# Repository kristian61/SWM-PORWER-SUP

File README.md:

# SWM-PORWER-SUP – laboratorieforsyning 100 V / 40 A

**Status: uafsluttet konstruktionsudkast. Den komplette 4 kW strømforsyning er ikke leveret eller frigivet til fremstilling.**

## Download

Afleveringsfilerne ligger direkte i dette repository:

- [Dansk PDF-manual, 134 sider](https://github.com/kristian61/SWM-PORWER-SUP/raw/refs/heads/main/exports/manual_da.pdf)
- [Komplet projekt-ZIP med fabrikantdatablade, cirka 61 MB](https://github.com/kristian61/SWM-PORWER-SUP/raw/refs/heads/main/exports/psu_design_draft.zip)
- [Mindre projekt-ZIP uden fabrikantdatablade, cirka 15 MB](https://github.com/kristian61/SWM-PORWER-SUP/raw/refs/heads/main/exports/psu_design_compact.zip)
- [SHA-256-kontrolsummer](exports/download_SHA256SUMS.txt)

PDF, ZIP og kontrolrapporter er den kontrollerede CAD-aflevering fra 10. oktober 2026, før GitHub-upload. Deres bemærkninger om endnu ikke udført GitHub-publicering beskriver dette tidligere tidspunkt. Kildefilerne på main indeholder samme CAD og beregningsarbejde samt disse downloadhenvisninger. Upload betyder ingen frigivelse til fremstilling eller net-/effekttest. Nogle scripts i den mindre ZIP kræver originalerne fra den komplette pakke.

Krav: 230 V AC på en dedikeret 32 A kreds, isoleret og flydende 0–100 V udgang, op til 40 A og justerbar strømbegrænsning til små prøveprint.

## Konkrete delprojekter

| Delprojekt | Leveret | Kontrolstatus |
|---|---|---|
| Passivt måle-/testkort | Native KiCad-diagram og fuldt routet 110 × 90 mm, 2-lags PCB, 11 testpunkter | ERC/DRC uden fejl, ingen åbne forbindelser, alle 52 pin/pad-forbindelser sammenholdt; HV-reglernes aktivering afprøvet |
| LTC3779-effektfase | To-siders diagram, lokal controller-symbol/footprint, BOM, 19 testpunkter og fuldt routet 135 × 90 mm PCB i fire lag | ERC/DRC/paritet uden fejl, ingen åbne forbindelser; 175 logiske pins og alle 191 fysiske pads kontrolleret |
| Isoleret netdel | Native chassisdiagram for 2 × RSP-3000-48 ved 55 V hver, separate enable-kredse, lokale senseledninger og diodekrav | Officielle producentdata og terminalforbindelser kontrolleret, ERC bestået; ingen net-PCB eller kvalificeret systemintegration |
| Analogt CV/CC-styrekort | Separat forsøgsdiagram, fuldt routet 180 × 150 mm PCB, komponentliste og 16 testpunkter til én effektfase | ERC/DRC/paritet bestået, alle 211 forbindelser stemmer; regulering og fejlrespons utestet, omfatter ikke 0 V, milliamperebeskyttelse eller 40 A |

Effektfaseudkastet har fast 99,6 V, 10 A som uverificeret udviklingsmål og en intern fast strømgrænse omkring 12,5 A. Det er ikke en 0–100 V / 40 A laboratorieforsyning og har ingen justerbar laboratorie-CC. Der er endnu ingen hardwaretest af nogen af kortene.

Det separate styrekort undersøger en positiv VFB-injektion til CV og en ITH-clamp til CC. Det er ikke integreret i den oprindelige faste effektfase. Nominelle kommandoer dækker cirka 1,2–100 V og 0–10 A, men de aktuelle hardwarevinduer slukker ved strømkommandoer under cirka 0,21 A. Det kan derfor ikke bruges som dokumenteret beskyttelse af et lille opamp-print.

## Filer

- `design/measurement/measurement.kicad_pro`: målekortets native KiCad-projekt.
- `design/power/power_phase.kicad_pro`: det uafsluttede enkeltfase-projekt.
- `design/frontend/frontend.kicad_pro`: netmodulernes chassisforbindelser; `exports/frontend/frontend.pdf` er det to-siders PDF-diagram.
- `design/control/control.kicad_pro`: separat eksperimentelt analogt styrekort med routet PCB.
- `bom/measurement.csv` og `bom/power-phase.csv`: alle komponentreferencer, værdier, mængder, footprints, funktioner og indkøbs-/reviewstatus for hvert kort. Referencer som R1 og J1 starter forfra på hvert delprojekt.
- `bom/current-draft.csv`: samlet komponentoversigt med eksplicit kortnavn; den er ikke en komplet 4 kW-stykliste.
- `bom/critical-components.csv` og `docs/component-qualification.md`: 85 kritiske komponentposter med fabrikantdata, pinout, betingelser og åbne valg.
- `design/control/studies/`, `bom/phase-balancing-study.csv` og `docs/phase-balancing.md`: nyt énkanals fasestrømstudie og model af fire uafhængige strømservoer; ikke integreret i de routede kort.
- `docs/bus-disconnect-design.md`: betinget dimensionering af fysisk busafbrydelse; komponent- og transientkvalifikation mangler.
- `docs/final-status.md`: afsluttende status opdelt i CAD, kontroller, beregninger, simulering og fysisk validering.
- `bom/frontend.csv`: netmoduler og alle viste chassisdele; manglende varenumre/rating står som krav, ikke indkøbsfrigivne komponenter.
- `bom/control.csv` og `docs/control.md`: styrekortets komponenter, funktion, stik, testpunkter og aktuelle begrænsninger.
- `docs/control-layout.md`, `docs/power-analysis.md`, `docs/bus-protection.md` og `docs/low-current-output.md`: layout, tab/ripple/loop-modeller, busfejl og mA-/0 V-undersøgelse.
- `docs/low-current-loop.md`: separat antaget post-bulk-strømservo og varm-SOA-begrænsning; ingen frigivet lavstrøms-PCB.
- `docs/power-layout.md` og `exports/power/remaining_connections.json`: effektkortets strømbaner, kobberbudget, regler og konkrete routingrester.
- `docs/manual.md` og `docs/power-phase.md`: funktion, stik, testpunkter og fejlfinding.
- `docs/krav.md`, `docs/architecture-research.md`, `docs/frontend-selection.md` og `docs/protection-and-test-plan.md`: krav, effektbudget, isolation/netdel og fysisk valideringsplan.
- `exports/manual_da.pdf`: samlet dansk projektmanual.
- `exports/measurement/` og `exports/power/`: PDF-diagrammer og PCB-visninger.
- `exports/verification/`: kontroller og samlet status. Ingen Gerber-frigivelse.
- `exports/verification/project_status.json`: samlet CAD-status, beregningsrapporter, kildehashes og manglende hardwarevalidering.
- `references/`: hentede officielle producentdatablade og referencekredsløb.

## KiCad i cloudmiljøet

KiCad 9.0.2 er allerede installeret. Brug wrapperen, fordi hjemmemappen er skrivebeskyttet:

```sh
cd /workspace/SWM-PORWER-SUP
bin/kicad-env kicad-cli version
bin/kicad-env /usr/bin/python3 scripts/validate_kicad.py
bin/kicad-env /usr/bin/python3 scripts/check_inventory.py
bin/kicad-env /usr/bin/python3 scripts/validate_control_layout.py
```

Python PCB-API'en findes i `/usr/bin/python3`, ikke standard-Python. Brug den eksisterende checkout; cloudopgaven er allerede isoleret, så opret ikke en Git worktree som opstartstrin.

Kun ved bevidst regeneration af genererede filer:

```sh
bin/kicad-env /usr/bin/python3 scripts/measurement_gen.py
bin/kicad-env /usr/bin/python3 scripts/power_phase_gen.py
bin/kicad-env /usr/bin/python3 scripts/frontend_gen.py
bin/kicad-env /usr/bin/python3 scripts/control_gen.py
bin/kicad-env /usr/bin/python3 scripts/control_route.py
/usr/bin/python3 scripts/package_draft.py --metadata-only
/usr/bin/python3 scripts/project_status.py
/usr/bin/python3 scripts/render_manual.py
/usr/bin/python3 scripts/package_draft.py
```

Beregningsmodeller kan køres særskilt med `/usr/bin/python3`: design_calcs.py, power_analysis.py, control_limits.py, low_current_calcs.py, low_current_loop.py, phase_balance_analysis.py, bus_protection_calcs.py og bus_disconnect_envelope.py. Kør design_calcs.py efter bus_disconnect_envelope.py for det konsistente tillægsbudget. De aktuelle resultater og modelantagelser ligger i exports/analysis/.

Generatorerne overskriver deres genererede KiCad-filer. Bevar brugerændringer først. Efter control_gen.py skal control_route.py genoprette routingen. Den afsluttende validate_control_layout.py opdaterer aktuel status; summary_pre_route.json viser generatorstadiet. power_phase_gen.py genafspiller den gemte slutrouting fra power_routing_plan.json; en isoleret regeneration er kontrolleret.

## Hvad der blokerer den komplette konstruktion

Front-endens arbejdsvalg er nu dokumenteret: 2 × RSP-3000-48 ved 55 V giver nominelt 110 V. Der mangler modelkvalifikation af seriedrift/flydende offset, endelige chassis-/effektkomponenter, busbeskyttelse, færdig og integreret CV/CC samt 0 V-regulering, lavstrømsbeskyttelse, firefaset systemintegration og fysisk validering. Modulernes OVP kan tillade samlet 134,4 V threshold og ukendt oversving; det overholder ikke automatisk effektfasens 120 V-proceduregrænse. Færdig CAD-routing ændrer ikke disse funktionelle og sikkerhedsmæssige blokeringer.

Analog Devices, TI, `meanwell.com` og aktuelle Infineon-produkt-/assetadresser kan nås, og de læste originaler er gemt i `references/`. `www.diodes.com` gav fortsat HTTP 403 ved de seneste normale forsøg. Netværksdomæner og genbrugelige KiCad-opstartsinstruktioner er gemt i miljøkladden. Gennemgå og gem ændringerne i miljøindstillingerne for genbrug; en kladdesave publicerer ikke miljøet. Publicering og afprøvning i en ny task er ikke udført.

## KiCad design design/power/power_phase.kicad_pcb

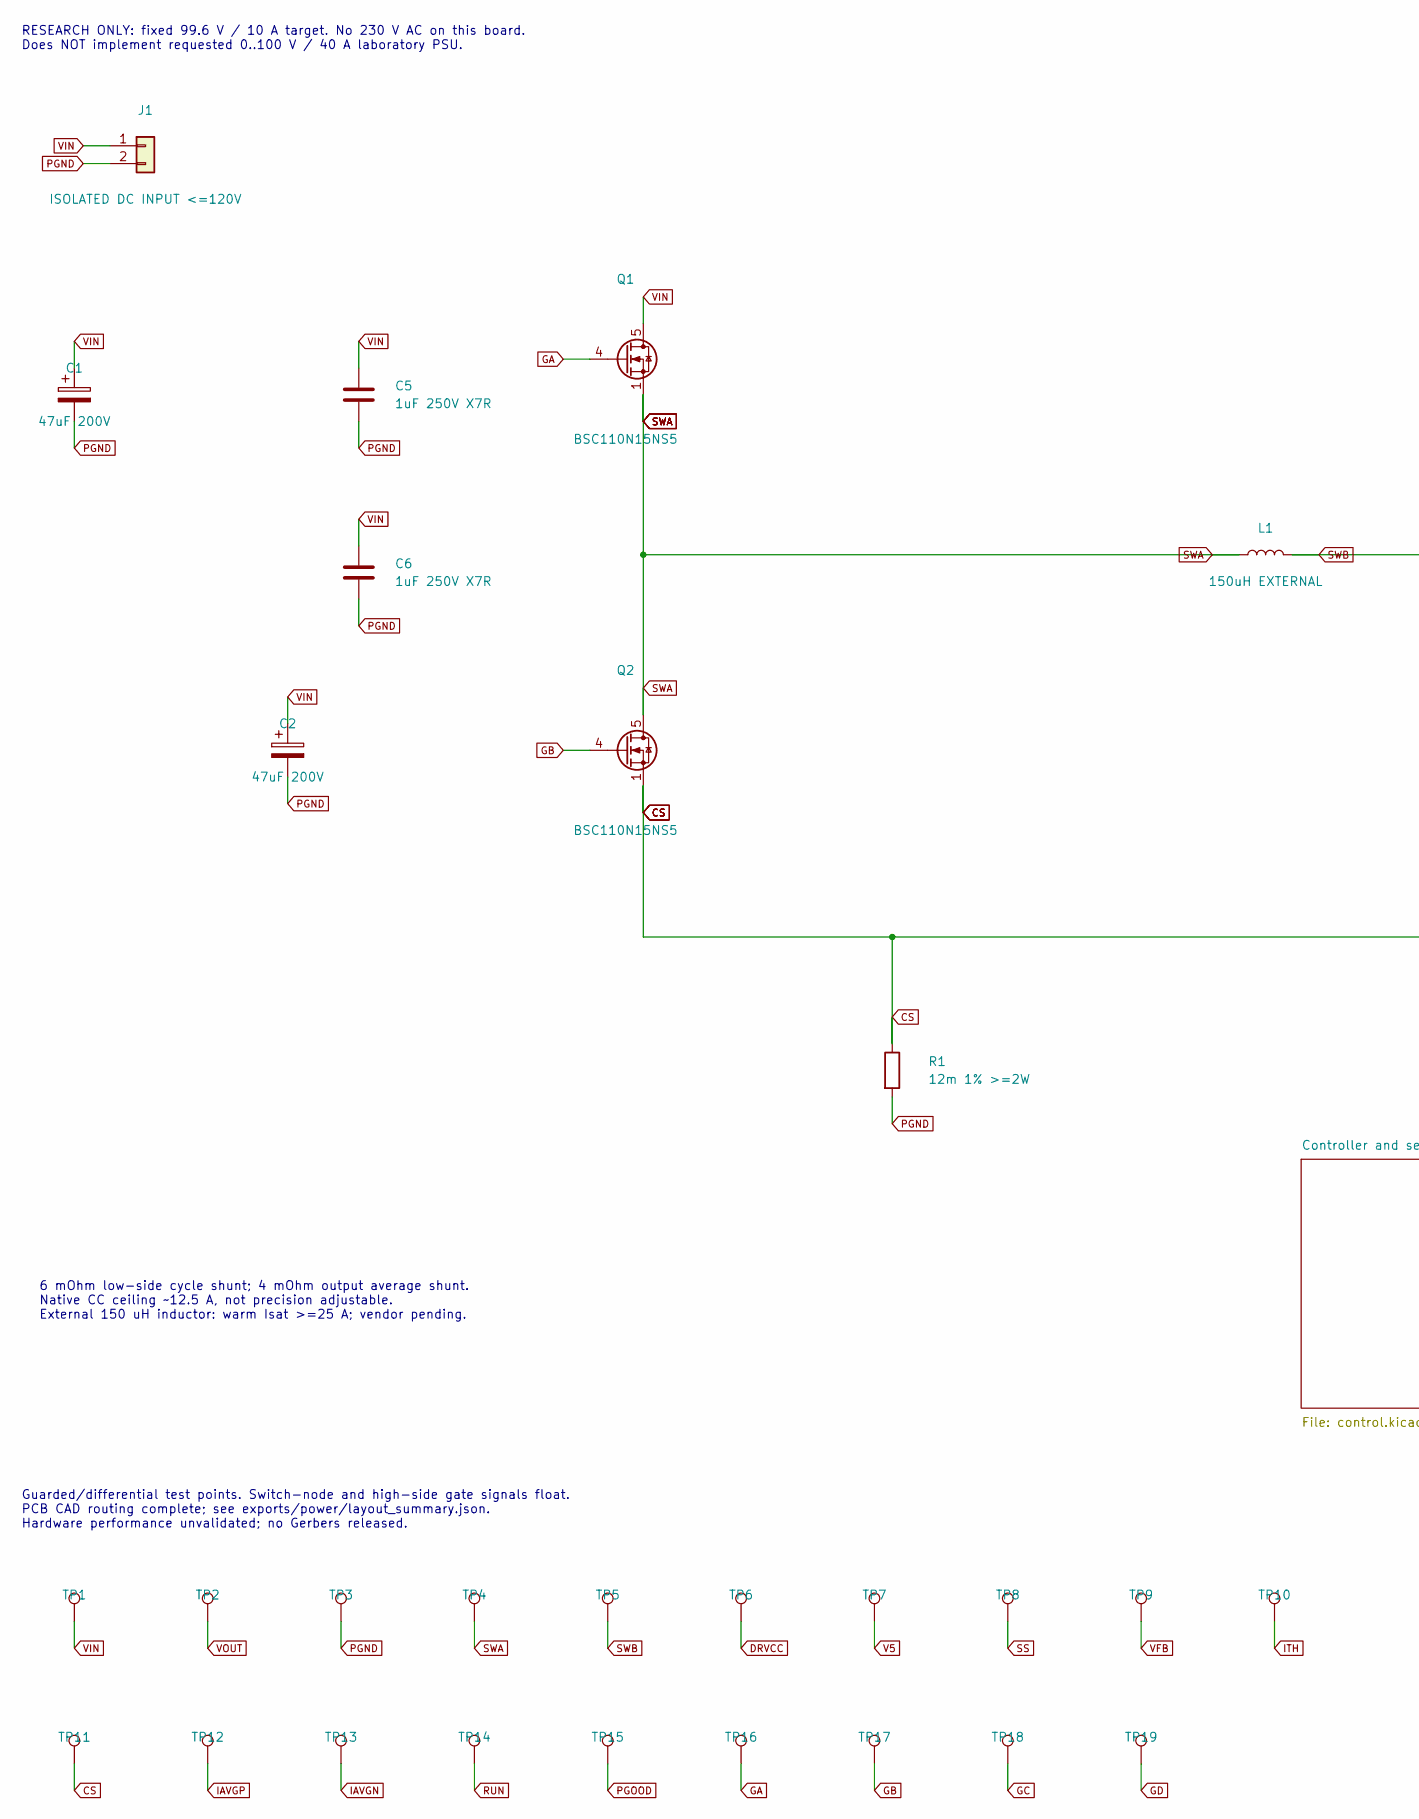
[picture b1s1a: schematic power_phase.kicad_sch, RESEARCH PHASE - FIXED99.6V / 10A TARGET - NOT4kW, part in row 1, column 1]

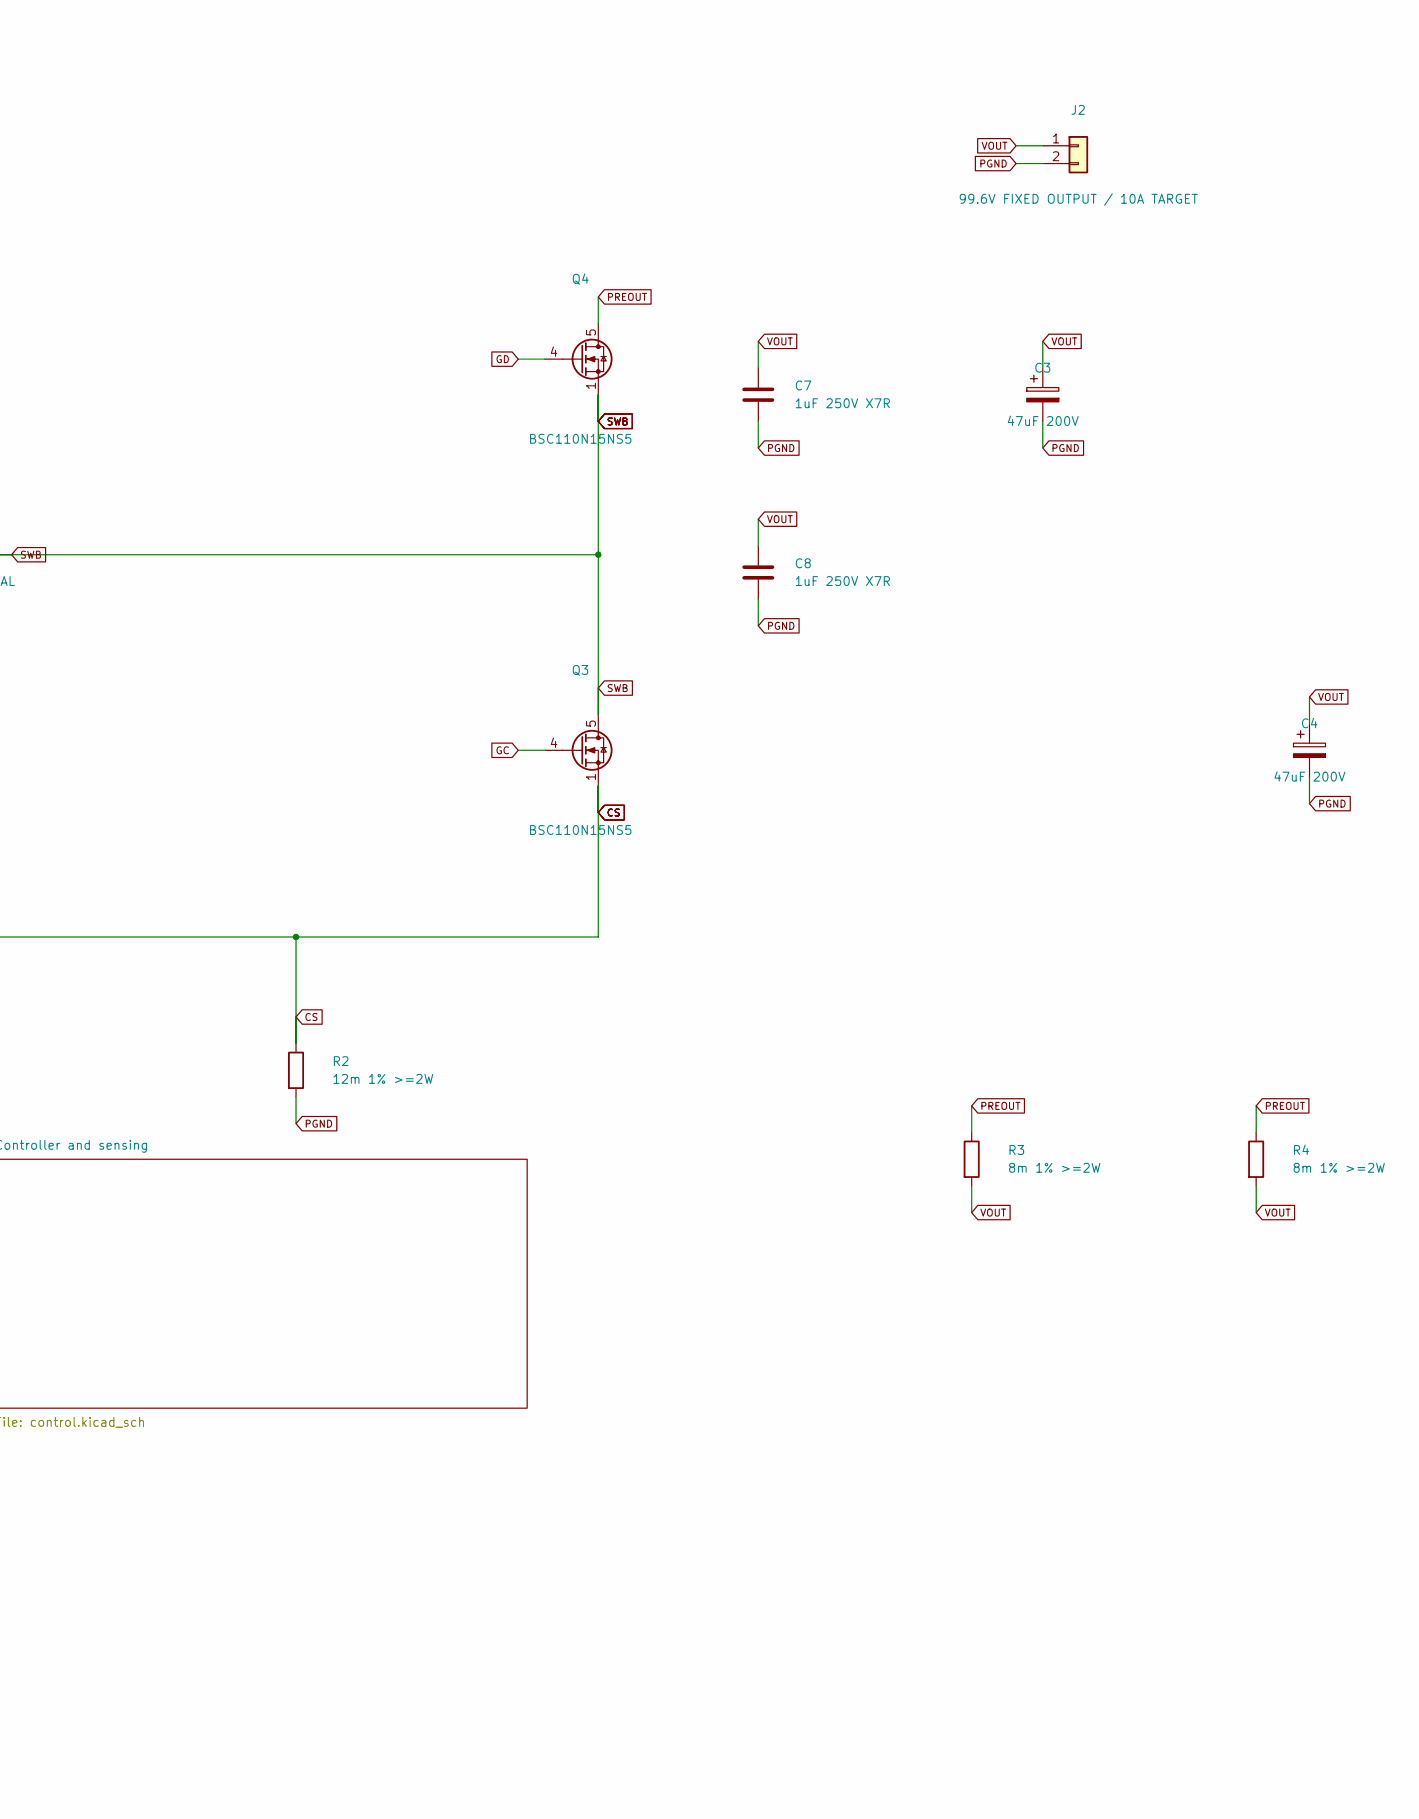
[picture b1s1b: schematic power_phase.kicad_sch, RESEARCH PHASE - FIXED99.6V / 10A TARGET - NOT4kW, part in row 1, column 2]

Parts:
C1, C2, C3, C4: 47uF 200V; CP_Radial_D12.5mm_P5.00mm
C5, C6, C7, C8: 1uF 250V X7R; C_2220_5750Metric
J1: ISOLATED DC INPUT <=120V; TerminalBlock_RND_205-00241_1x02_P10.16mm_Horizontal
J2: 99.6V FIXED OUTPUT / 10A TARGET; TerminalBlock_RND_205-00241_1x02_P10.16mm_Horizontal
L1: 150uH EXTERNAL; TerminalBlock_RND_205-00241_1x02_P10.16mm_Horizontal
Q1, Q2, Q3, Q4: BSC110N15NS5; Infineon_PG-TDSON-8_6.15x5.15mm
R1, R2: 12m 1% >=2W; R_2512_6332Metric
R3, R4: 8m 1% >=2W; R_2512_6332Metric
TP1: VIN; TestPoint_THTPad_D2.0mm_Drill1.0mm
TP2: VOUT; TestPoint_THTPad_D2.0mm_Drill1.0mm
TP3: PGND; TestPoint_THTPad_D2.0mm_Drill1.0mm
TP4: SWA; TestPoint_THTPad_D2.0mm_Drill1.0mm
TP5: SWB; TestPoint_THTPad_D2.0mm_Drill1.0mm
TP6: DRVCC; TestPoint_THTPad_D2.0mm_Drill1.0mm
TP7: V5; TestPoint_THTPad_D2.0mm_Drill1.0mm
TP8: SS; TestPoint_THTPad_D2.0mm_Drill1.0mm
TP9: VFB; TestPoint_THTPad_D2.0mm_Drill1.0mm
TP10: ITH; TestPoint_THTPad_D2.0mm_Drill1.0mm
TP11: CS; TestPoint_THTPad_D2.0mm_Drill1.0mm
TP12: IAVGP; TestPoint_THTPad_D2.0mm_Drill1.0mm
TP13: IAVGN; TestPoint_THTPad_D2.0mm_Drill1.0mm
TP14: RUN; TestPoint_THTPad_D2.0mm_Drill1.0mm
TP15: PGOOD; TestPoint_THTPad_D2.0mm_Drill1.0mm
TP16: GA; TestPoint_THTPad_D2.0mm_Drill1.0mm
TP17: GB; TestPoint_THTPad_D2.0mm_Drill1.0mm
TP18: GC; TestPoint_THTPad_D2.0mm_Drill1.0mm
TP19: GD; TestPoint_THTPad_D2.0mm_Drill1.0mm

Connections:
CS: Q2.1 (S), Q2.2 (S), Q2.3 (S), Q3.1 (S), Q3.2 (S), Q3.3 (S), R1.1, R2.1, TP11.1; also elsewhere on the board
DRVCC: TP6.1; also elsewhere on the board
GA: Q1.4 (G), TP16.1; also elsewhere on the board
GB: Q2.4 (G), TP17.1; also elsewhere on the board
GC: Q3.4 (G), TP18.1; also elsewhere on the board
GD: Q4.4 (G), TP19.1; also elsewhere on the board
IAVGN: TP13.1; also elsewhere on the board
IAVGP: TP12.1; also elsewhere on the board
ITH: TP10.1; also elsewhere on the board
PGND: C1.2, C2.2, C3.2, C4.2, C5.2, C6.2, C7.2, C8.2, J1.2, J2.2, R1.2, R2.2, TP3.1; also elsewhere on the board
PGOOD: TP15.1; also elsewhere on the board
PREOUT: Q4.5 (D), R3.1, R4.1; also elsewhere on the board
RUN: TP14.1; also elsewhere on the board
SS: TP8.1; also elsewhere on the board
SWA: L1.1, Q1.1 (S), Q1.2 (S), Q1.3 (S), Q2.5 (D), TP4.1; also elsewhere on the board
SWB: L1.2, Q3.5 (D), Q4.1 (S), Q4.2 (S), Q4.3 (S), TP5.1; also elsewhere on the board
V5: TP7.1; also elsewhere on the board
VFB: TP9.1; also elsewhere on the board
VIN: C1.1, C2.1, C5.1, C6.1, J1.1, Q1.5 (D), TP1.1; also elsewhere on the board
VOUT: C3.1, C4.1, C7.1, C8.1, J2.1, R3.2, R4.2, TP2.1; also elsewhere on the board

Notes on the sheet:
RESEARCH ONLY: fixed 99.6 V / 10 A target. No 230 V AC on this board. Does NOT implement requested 0..100 V / 40 A laboratory PSU.
6 mOhm low-side cycle shunt; 4 mOhm output average shunt. Native CC ceiling ~12.5 A, not precision adjustable. External 150 uH inductor: warm Isat >=25 A; vendor pending.
Guarded/differential test points. Switch-node and high-side gate signals float. PCB CAD routing complete; see exports/power/layout_summary.json. Hardware performance unvalidated; no Gerbers released.

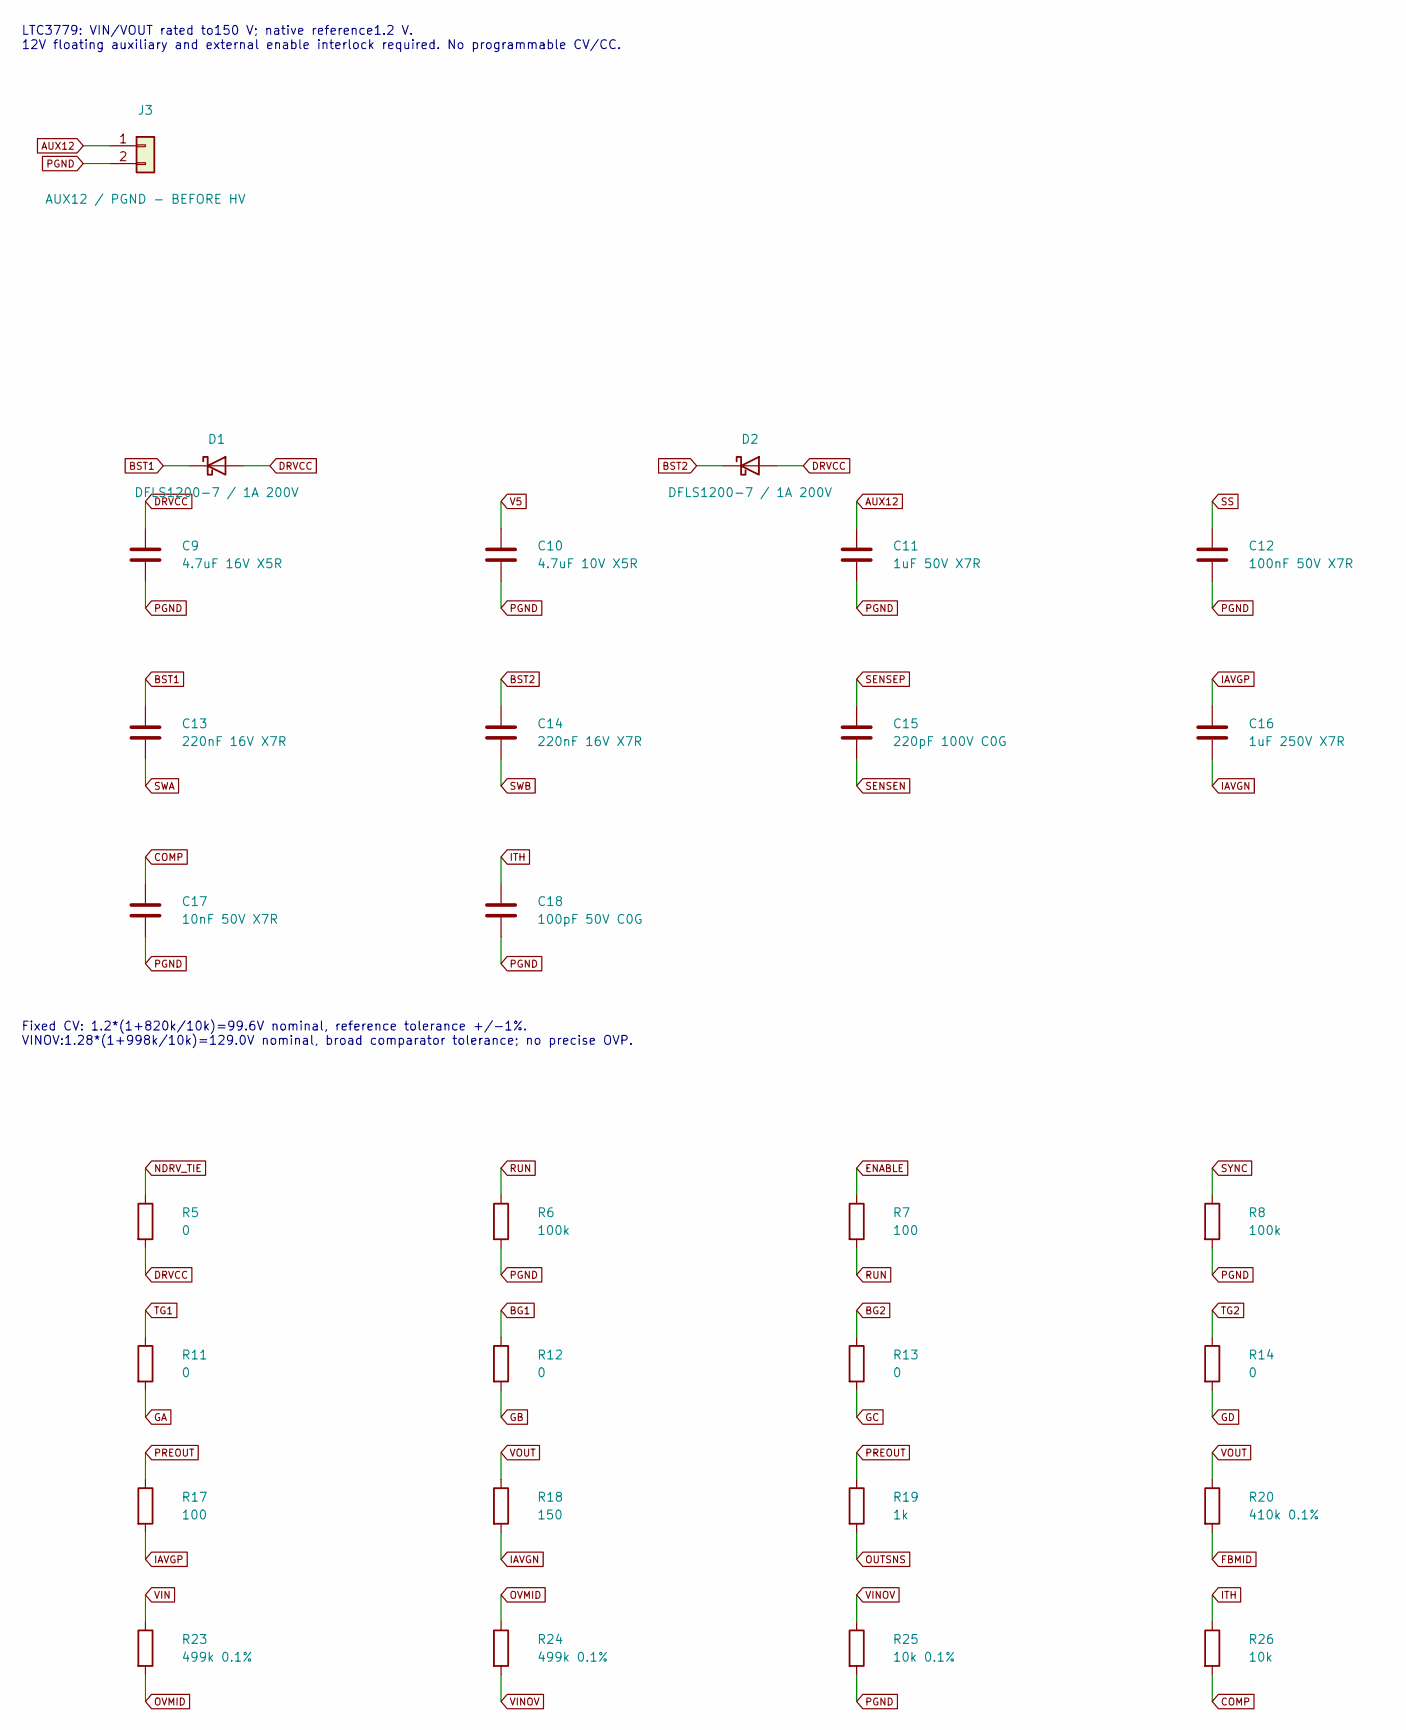
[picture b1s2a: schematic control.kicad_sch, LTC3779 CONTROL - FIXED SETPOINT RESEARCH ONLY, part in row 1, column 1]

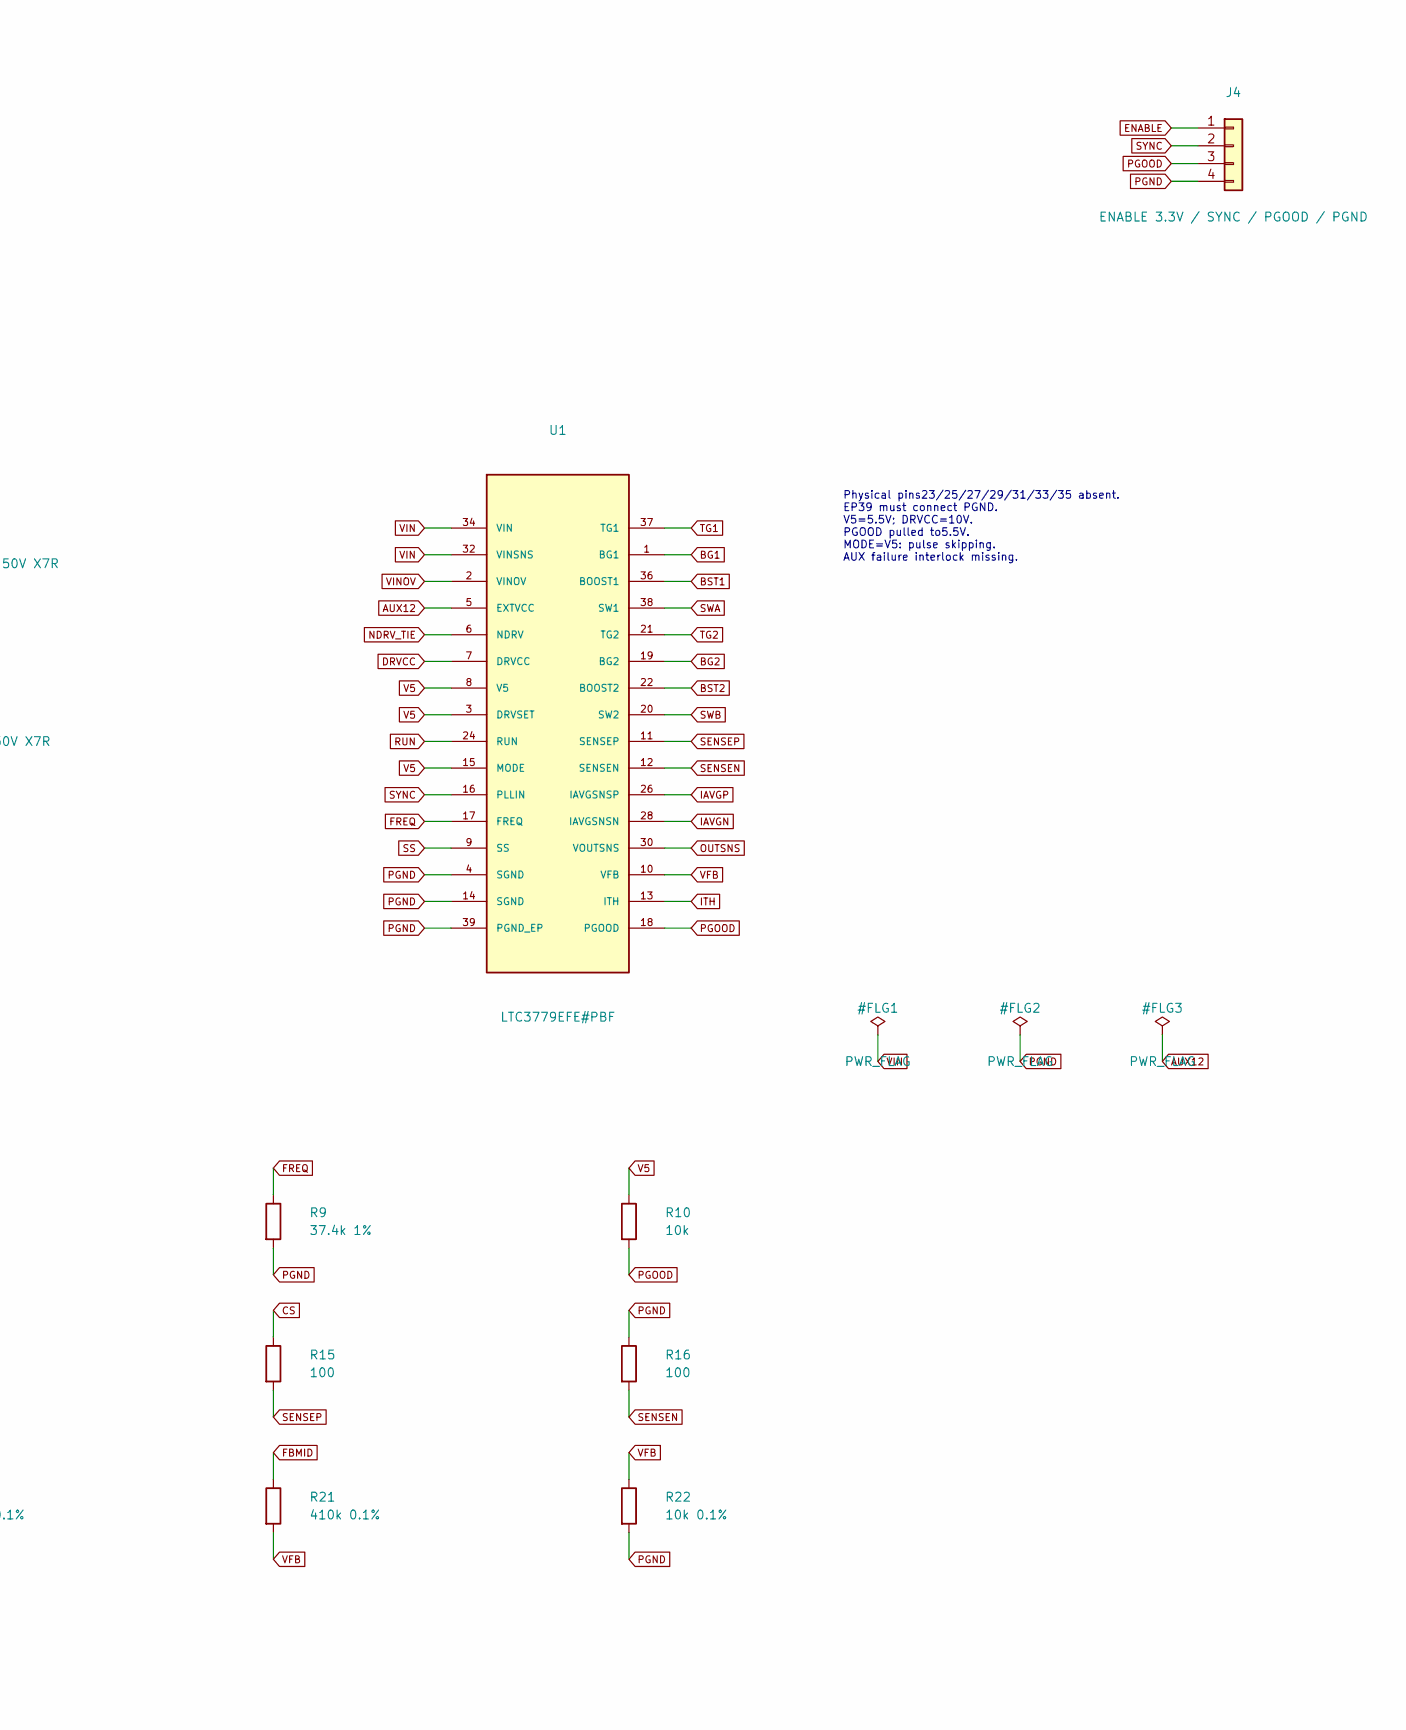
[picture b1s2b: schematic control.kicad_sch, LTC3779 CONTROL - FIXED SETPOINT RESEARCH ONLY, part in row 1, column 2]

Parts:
C9: 4.7uF 16V X5R; C_0603_1608Metric
C10: 4.7uF 10V X5R; C_0603_1608Metric
C11: 1uF 50V X7R; C_0603_1608Metric
C12: 100nF 50V X7R; C_0603_1608Metric
C13, C14: 220nF 16V X7R; C_0603_1608Metric
C15: 220pF 100V C0G; C_0603_1608Metric
C16: 1uF 250V X7R; C_2220_5750Metric
C17: 10nF 50V X7R; C_0603_1608Metric
C18: 100pF 50V C0G; C_0603_1608Metric
D1, D2: DFLS1200-7 / 1A 200V; D_PowerDI-123
J3: AUX12 / PGND - BEFORE HV; PinHeader_1x02_P2.54mm_Vertical
J4: ENABLE 3.3V / SYNC / PGOOD / PGND; PinHeader_1x04_P2.54mm_Vertical
R5, R11, R12, R13, R14: 0; R_0603_1608Metric
R6, R8: 100k; R_0603_1608Metric
R7, R15, R16, R17: 100; R_0603_1608Metric
R9: 37.4k 1%; R_0603_1608Metric
R10, R26: 10k; R_0603_1608Metric
R18: 150; R_0603_1608Metric
R19: 1k; R_0603_1608Metric
R20, R21: 410k 0.1%; R_1206_3216Metric
R22, R25: 10k 0.1%; R_0603_1608Metric
R23, R24: 499k 0.1%; R_1206_3216Metric
U1: LTC3779EFE#PBF; LTC3779_FE38_31_EP

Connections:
AUX12: C11.1, J3.1, U1.5 (EXTVCC)
BG1: R12.1, U1.1 (BG1)
BG2: R13.1, U1.19 (BG2)
BST1: C13.1, D1.1 (K), U1.36 (BOOST1)
BST2: C14.1, D2.1 (K), U1.22 (BOOST2)
COMP: C17.1, R26.2
CS: R15.1; also elsewhere on the board
DRVCC: C9.1, D1.2 (A), D2.2 (A), R5.2, U1.7 (DRVCC); also elsewhere on the board
ENABLE: J4.1, R7.1
FBMID: R20.2, R21.1
FREQ: R9.1, U1.17 (FREQ)
GA: R11.2; also elsewhere on the board
GB: R12.2; also elsewhere on the board
GC: R13.2; also elsewhere on the board
GD: R14.2; also elsewhere on the board
IAVGN: C16.2, R18.2, U1.28 (IAVGSNSN); also elsewhere on the board
IAVGP: C16.1, R17.2, U1.26 (IAVGSNSP); also elsewhere on the board
ITH: C18.1, R26.1, U1.13 (ITH); also elsewhere on the board
NDRV_TIE: R5.1, U1.6 (NDRV)
OUTSNS: R19.2, U1.30 (VOUTSNS)
OVMID: R23.2, R24.1
PGND: C9.2, C10.2, C11.2, C12.2, C17.2, C18.2, J3.2, J4.4, R6.2, R8.2, R9.2, R16.1, R22.2, R25.2, U1.4 (SGND), U1.14 (SGND), U1.39 (PGND_EP); also elsewhere on the board
PGOOD: J4.3, R10.2, U1.18 (PGOOD); also elsewhere on the board
PREOUT: R17.1, R19.1; also elsewhere on the board
RUN: R6.1, R7.2, U1.24 (RUN); also elsewhere on the board
SENSEN: C15.2, R16.2, U1.12 (SENSEN)
SENSEP: C15.1, R15.2, U1.11 (SENSEP)
SS: C12.1, U1.9 (SS); also elsewhere on the board
SWA: C13.2, U1.38 (SW1); also elsewhere on the board
SWB: C14.2, U1.20 (SW2); also elsewhere on the board
SYNC: J4.2, R8.1, U1.16 (PLLIN)
TG1: R11.1, U1.37 (TG1)
TG2: R14.1, U1.21 (TG2)
V5: C10.1, R10.1, U1.3 (DRVSET), U1.8 (V5), U1.15 (MODE); also elsewhere on the board
VFB: R21.2, R22.1, U1.10 (VFB); also elsewhere on the board
VIN: R23.1, U1.32 (VINSNS), U1.34 (VIN); also elsewhere on the board
VINOV: R24.2, R25.1, U1.2 (VINOV)
VOUT: R18.1, R20.1; also elsewhere on the board

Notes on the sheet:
LTC3779: VIN/VOUT rated to150 V; native reference1.2 V. 12V floating auxiliary and external enable interlock required. No programmable CV/CC.
Fixed CV: 1.2*(1+820k/10k)=99.6V nominal, reference tolerance +/-1%. VINOV:1.28*(1+998k/10k)=129.0V nominal, broad comparator tolerance; no precise OVP.
Physical pins23/25/27/29/31/33/35 absent. EP39 must connect PGND. V5=5.5V; DRVCC=10V. PGOOD pulled to5.5V. MODE=V5: pulse skipping. AUX failure interlock missing.

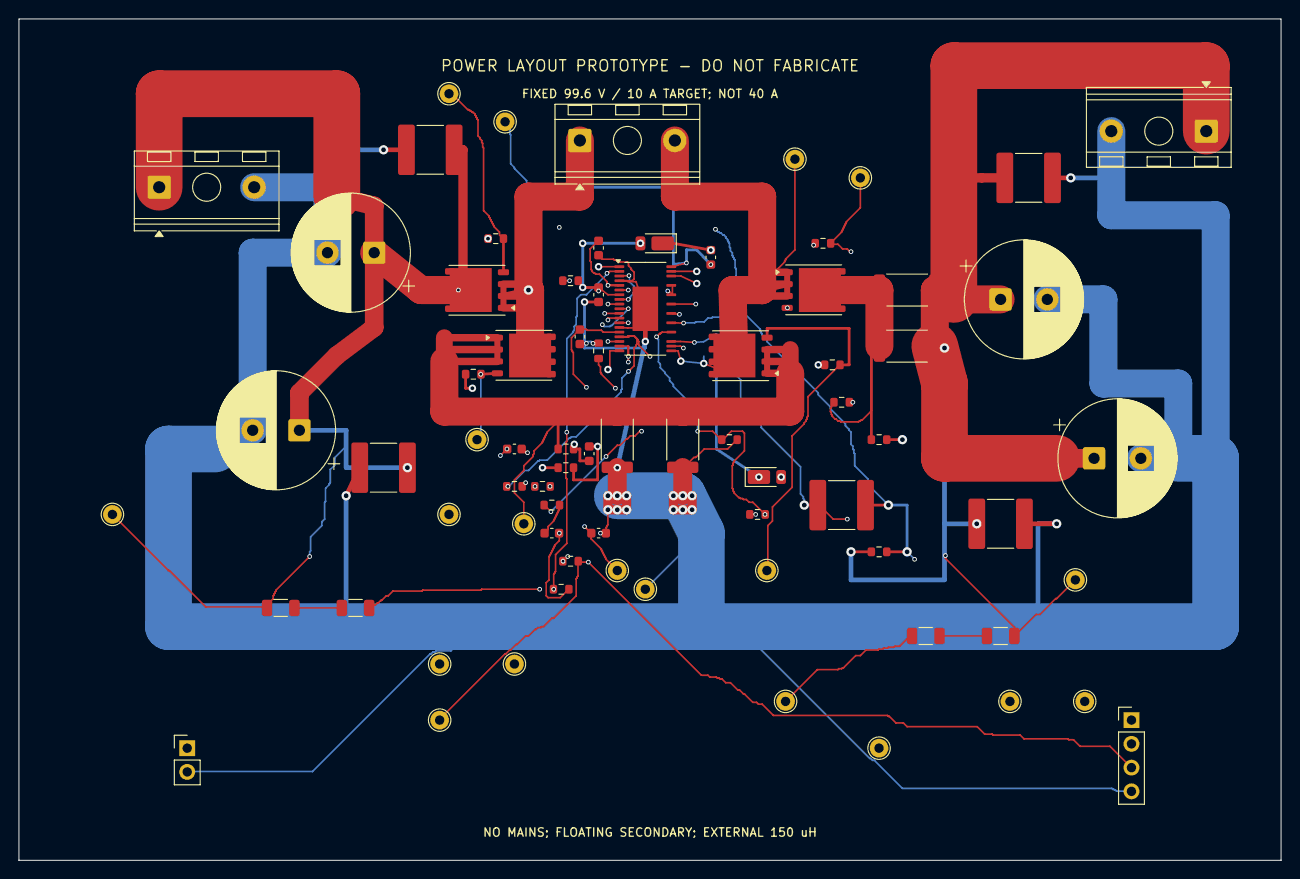
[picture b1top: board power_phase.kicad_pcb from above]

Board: 4 copper layers, 135.0 x 90.0 mm, 75 parts (1 on the bottom side), 38 nets.

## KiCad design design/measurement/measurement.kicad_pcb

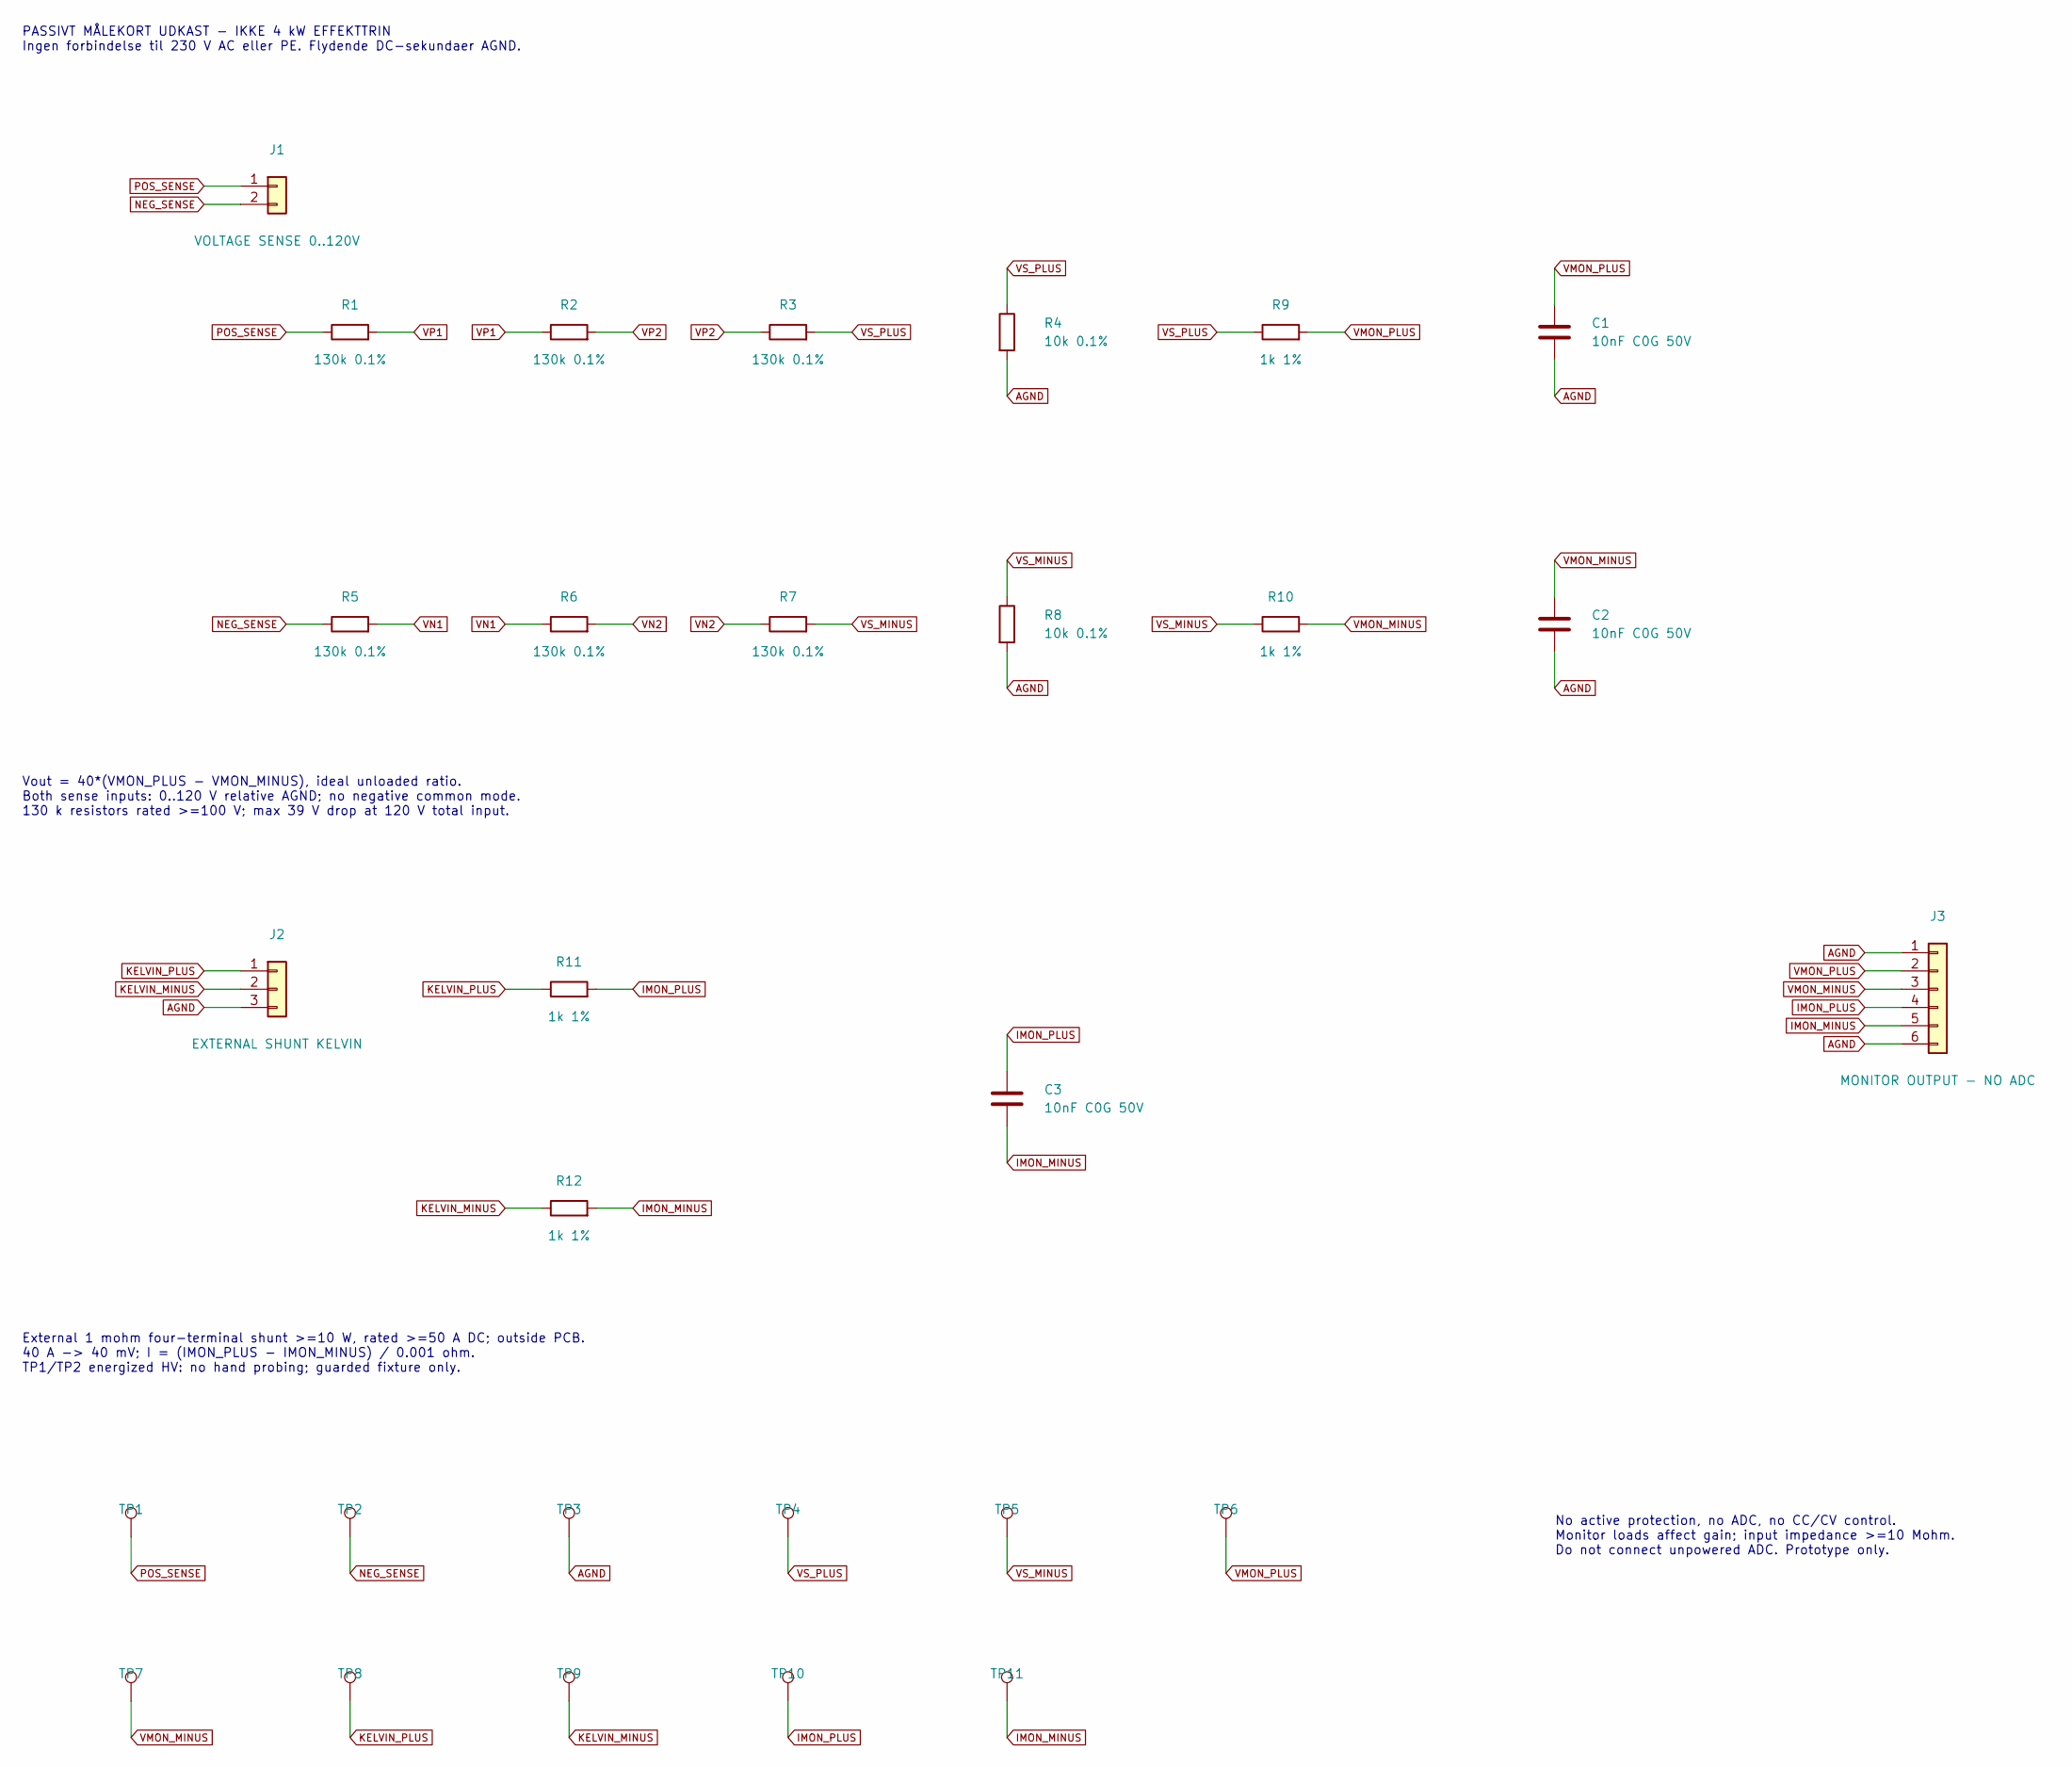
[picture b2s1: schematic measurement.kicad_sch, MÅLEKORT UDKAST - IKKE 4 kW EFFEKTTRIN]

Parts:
C1, C2, C3: 10nF C0G 50V; C_0603_1608Metric
J1: VOLTAGE SENSE 0..120V; TerminalBlock_RND_205-00241_1x02_P10.16mm_Horizontal
J2: EXTERNAL SHUNT KELVIN; TerminalBlock_Phoenix_MKDS-1,5-3-5.08_1x03_P5.08mm_Horizont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
J3: MONITOR OUTPUT - NO ADC; PinHeader_1x06_P2.54mm_Vertical
R1, R2, R3, R5, R6, R7: 130k 0.1%; R_1206_3216Metric
R4, R8: 10k 0.1%; R_1206_3216Metric
R9, R10, R11, R12: 1k 1%; R_0603_1608Metric
TP1: POS_SENSE; TestPoint_THTPad_D2.0mm_Drill1.0mm
TP2: NEG_SENSE; TestPoint_THTPad_D2.0mm_Drill1.0mm
TP3: AGND; TestPoint_THTPad_D2.0mm_Drill1.0mm
TP4: VS_PLUS; TestPoint_THTPad_D2.0mm_Drill1.0mm
TP5: VS_MINUS; TestPoint_THTPad_D2.0mm_Drill1.0mm
TP6: VMON_PLUS; TestPoint_THTPad_D2.0mm_Drill1.0mm
TP7: VMON_MINUS; TestPoint_THTPad_D2.0mm_Drill1.0mm
TP8: KELVIN_PLUS; TestPoint_THTPad_D2.0mm_Drill1.0mm
TP9: KELVIN_MINUS; TestPoint_THTPad_D2.0mm_Drill1.0mm
TP10: IMON_PLUS; TestPoint_THTPad_D2.0mm_Drill1.0mm
TP11: IMON_MINUS; TestPoint_THTPad_D2.0mm_Drill1.0mm

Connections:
AGND: C1.2, C2.2, J2.3, J3.1, J3.6, R4.2, R8.2, TP3.1
IMON_MINUS: C3.2, J3.5, R12.2, TP11.1
IMON_PLUS: C3.1, J3.4, R11.2, TP10.1
KELVIN_MINUS: J2.2, R12.1, TP9.1
KELVIN_PLUS: J2.1, R11.1, TP8.1
NEG_SENSE: J1.2, R5.1, TP2.1
POS_SENSE: J1.1, R1.1, TP1.1
VMON_MINUS: C2.1, J3.3, R10.2, TP7.1
VMON_PLUS: C1.1, J3.2, R9.2, TP6.1
VN1: R5.2, R6.1
VN2: R6.2, R7.1
VP1: R1.2, R2.1
VP2: R2.2, R3.1
VS_MINUS: R7.2, R8.1, R10.1, TP5.1
VS_PLUS: R3.2, R4.1, R9.1, TP4.1

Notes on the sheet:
PASSIVT MÅLEKORT UDKAST - IKKE 4 kW EFFEKTTRIN Ingen forbindelse til 230 V AC eller PE. Flydende DC-sekundaer AGND.
Vout = 40*(VMON_PLUS - VMON_MINUS), ideal unloaded ratio. Both sense inputs: 0..120 V relative AGND; no negative common mode. 130 k resistors rated >=100 V; max 39 V drop at 120 V total input.
External 1 mohm four-terminal shunt >=10 W, rated >=50 A DC; outside PCB. 40 A -> 40 mV; I = (IMON_PLUS - IMON_MINUS) / 0.001 ohm. TP1/TP2 energized HV: no hand probing; guarded fixture only.
No active protection, no ADC, no CC/CV control. Monitor loads affect gain; input impedance >=10 Mohm. Do not connect unpowered ADC. Prototype only.
